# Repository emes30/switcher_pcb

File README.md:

# Switcher 2.0 – 2 Channel WiFi Open Source Switch
This is fork from [this project](https://github.com/hborisov/switcher_pcb).
I've added support for two independent relays, two buttons and DS18B20 digital thermometer. 
It is compatibile with [Sonoff-Tasmota](https://github.com/arendst/Sonoff-Tasmota) firmware.

## Disclaimer
:warning: This device is meant to connect to AC MAINS. Be careful, if you have no experience, ask someone who has to assist you.

## Design
The board size is 46x46mm it shoud fit into standard electrical wall junction box where it is meant to be installed.

## Connections
Connections are very simple. 
1. Connect AC mains L, N to power line.
2. Connect your devices to OUT_1 and OUT_2. Maximum output power output is 400W. It is enough for light sources. It should not be used for wall sockets. For outputs above 200W consider attaching heatsinks to BT136's to dissipate heat.
3. Connect BTN_1 and BTN_2 to momentary buttons, notice that there is no high voltage on these buttons.

## Programming WiFi module
Board is designed to work with ESP8266 module ESP-01S, this is simplest and cheapest ESP module. Unfortunatelly you cannot program module in place, as there is no space for required pinheader. You should flash chip with [Sonoff-Tasmota](https://github.com/arendst/Sonoff-Tasmota) firmware and choose Sonoff Generic device. You need to program module only once, then you can update via web interface.

## Sensor
There is pinheader where you can connect 1-Wire DS18B20 digital thermometer. It uses BTN_1 pin so you can't use both DS18B20 and BTN_1.

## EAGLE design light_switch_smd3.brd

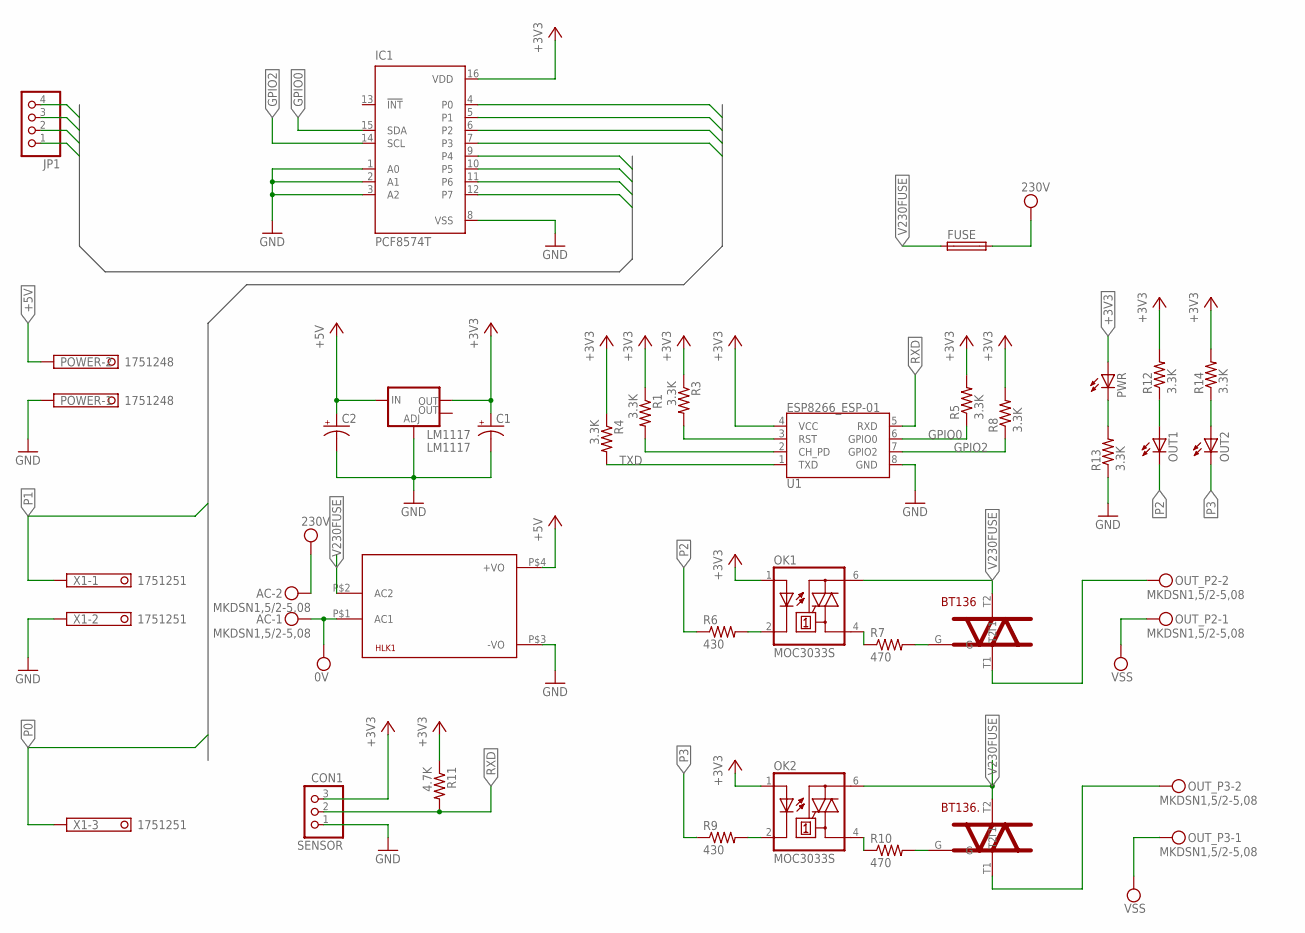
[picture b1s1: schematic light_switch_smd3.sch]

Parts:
AC: MKDSN1,5/2-5,08
BT136, BT136.: BT136; BT136-PKG
C1, C2: 10uF; A/3216-18R
FUSE: TE5
HLK1: HLK-PM013W; HLK-PM01
IC1: PCF8574T; SO16W
JP1: PINHD-1X4; 1X04
LM1117: LM1117; SOT223
OK1, OK2: MOC3033S; DIL6-SMD
OUT1, OUT2: LEDSML1206; SML1206
OUT_P2, OUT_P3: MKDSN1,5/2-5,08
POWER: 1751248
PWR: LEDSML1206; SML1206
R1, R3, R4, R5, R8, R12, R13, R14: 3.3K; R1206
R6, R9: 430; R1206
R7, R10: 470; R1206
R11: 4.7K; R1206
SENSOR: CON1; 1X03
U1: ESP8266_ESP-01
X1: 1751251

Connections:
+3V3: C1.+, IC1.16 (VDD), LM1117.2 (OUT), OK1.1 (A), OK2.1 (A), PWR.A, R1.1, R3.1, R4.1, R5.2, R8.2, R11.1, R12.2, R14.2, SENSOR.3, U1.4 (VCC)
+5V: C2.+, HLK1.P$4 (+VO), LM1117.3 (IN), POWER.2
CH_PD: R1.2, U1.2 (CH_PD)
GND: C1.-, C2.-, HLK1.P$3 (-VO), IC1.1 (A0), IC1.2 (A1), IC1.3 (A2), IC1.8 (VSS), LM1117.1 (ADJ), POWER.1, R13.1, SENSOR.1, U1.8 (GND), X1.2
GPIO0: IC1.15 (SDA), R5.1, U1.6 (GPIO0)
GPIO2: IC1.14 (SCL), R8.1, U1.7 (GPIO2)
unnamed: PWR.C, R13.2
unnamed: OK2.2 (C), R9.2
unnamed: OK2.4 (A1), R10.1
unnamed: BT136.T1, OUT_P2.2
unnamed: OK1.2 (C), R6.2
unnamed: BT136.G, R7.2
unnamed: OK1.4 (A1), R7.1
unnamed: BT136..T1, OUT_P3.2
unnamed: OUT1.A, R12.1
unnamed: OUT2.A, R14.1
unnamed: BT136..G, R10.2
P0: IC1.4 (P0), X1.3
P1: IC1.5 (P1), X1.1
P2: IC1.6 (P2), OUT1.C, R6.1
P3: IC1.7 (P3), OUT2.C, R9.1
P4: IC1.9 (P4), JP1.1
P5: IC1.10 (P5), JP1.2
P6: IC1.11 (P6), JP1.3
P7: IC1.12 (P7), JP1.4
RST: R3.2, U1.3 (RST)
RXD: R11.2, SENSOR.2, U1.5 (RXD)
TXD: R4.2, U1.1 (TXD)
V230FUSE: BT136.T2, BT136..T2, FUSE.1, HLK1.P$2 (AC2), OK1.6 (A2), OK2.6 (A2)
VPP: AC.2, FUSE.2
VSS: AC.1, HLK1.P$1 (AC1), OUT_P2.1, OUT_P3.1

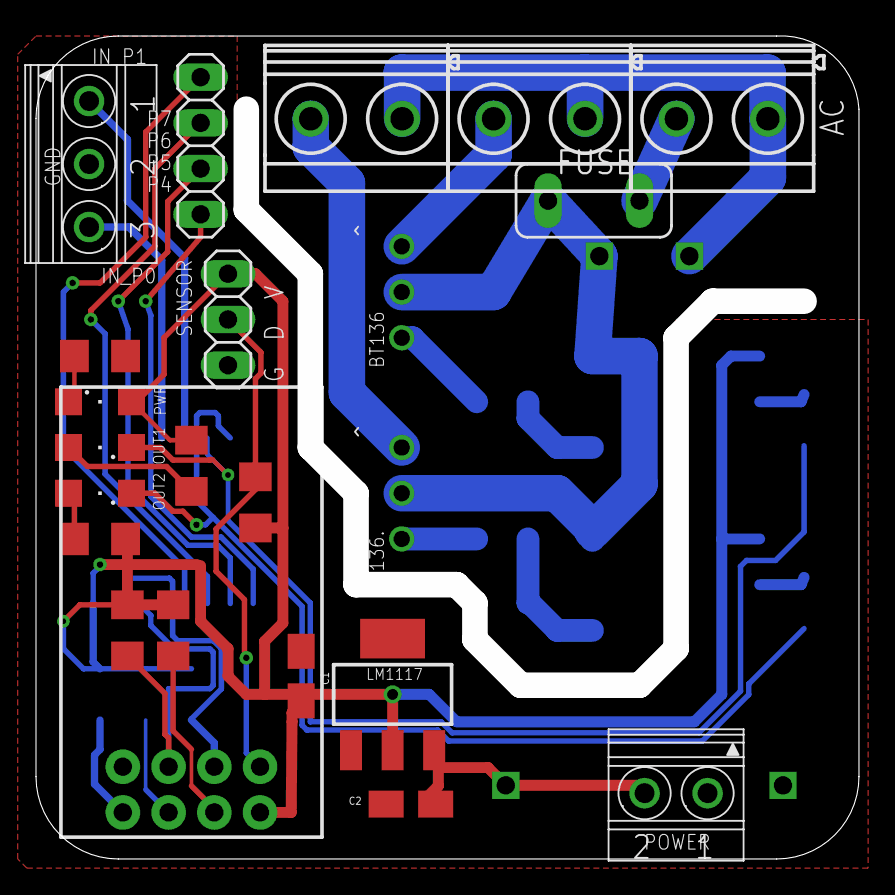
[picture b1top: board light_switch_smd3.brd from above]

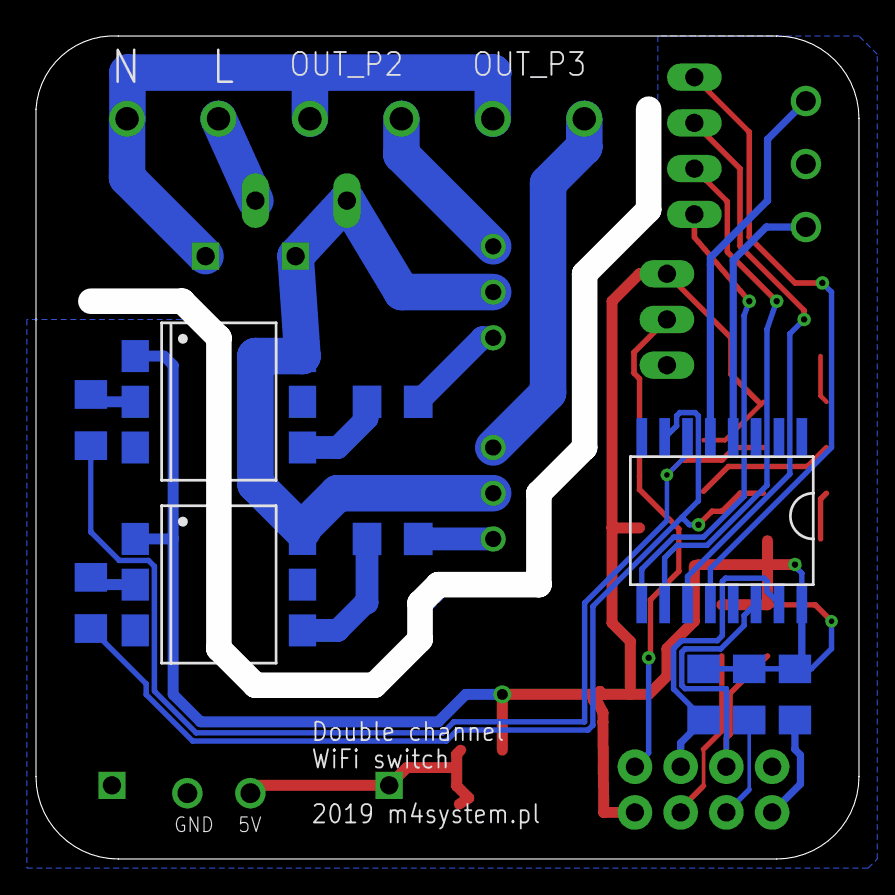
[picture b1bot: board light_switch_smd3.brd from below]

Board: 2 copper layers, 44.3 x 44.3 mm, 34 parts (10 on the bottom side), 31 nets.

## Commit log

2019-02-11 major update. added second relay circuit, redesigned board
2019-02-11 almost ready for production. some descriptions needs adjusting.
2019-02-11 minor bugs fixed
2019-02-11 sligthly bigger smd parts, for easier soldering
2019-02-25 kosmetyczne poprawki, wersja wysłana do produkcji
2019-02-25 added missing sensor data connection
2019-02-25 README.md update
2019-02-25 small fixes to be more ERC friendly
2019-04-04 routed missed track
2019-04-05 added LEDs, more rounded corners, +5V power connector
2019-05-14 added pcf8574 due to undefined state of GPIOs during boot
2019-05-15 DRC checked, no airwires
2020-01-06 added pinheader and small fixes
2020-01-07 descriptions adjusted

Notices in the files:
parts and their libraries:
SparkFun-PowerIC: Licensing: Creative Commons ShareAlike 4.0 International - https://creativecommons.org/licenses/by-sa/4.0
